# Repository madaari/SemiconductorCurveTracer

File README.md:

# SemiconductorCurveTracer
All the data related to Semiconductor Curve Tracer.

This Repo contains the design files, code files of every version of curve tracer
build at TI-CEPD.

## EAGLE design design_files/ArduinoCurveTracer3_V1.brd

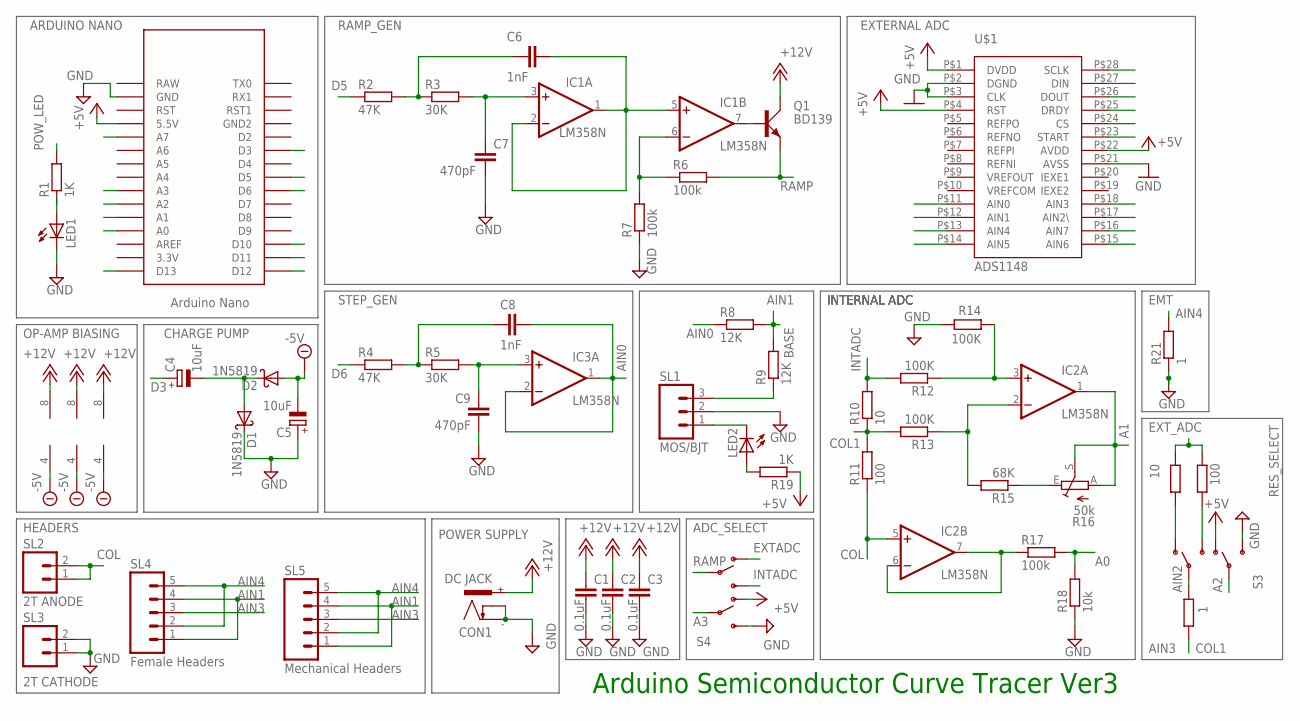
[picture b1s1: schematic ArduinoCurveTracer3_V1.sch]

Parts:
ARDUINONANO: NANO
C1, C2, C3: 0.1uF; C0805
C4, C5: 10uF; E2,5-5
C6: 1nF; C0603
C7: 470pF; C025-024X044
C8: 1nF; C025-024X044
C9: 470pF; C0805
CON1: DC JACK; NEB21R
D1, D2: 1N5819; DO41-10
IC1, IC2, IC3: LM358N; DIL08
LED1, LED2: LED3MM
Q1: BD139; TO126AV
R1, R19: 1K; 0207/10
R2: 47K; 0207/10
R3, R5: 30K; 0204/7
R4: 47K; 0204/7
R6: 100k; M0805
R7, R17: 100k; 0207/7
R8, R9: 12K; 0207/10
R10: 10; 0207/10
R11: 100; 0207/10
R12, R13: 100K; 0207/10
R14: 100K; 0204/7
R15: 68K; 0204/7
R16: 50k; S64W
R18: 10k; 0204/7
R21: 1; 0207/10
R22: 10; 0204/7
R23: 100; 0204/7
R24: 1; 0204/7
S3, S4: SWITCH-SPDTPTH2; SWITCHE-DPDT
SL1: MOS/BJT; 03P
SL2: 2T ANODE; 02P
SL3: 2T CATHODE; 02P
SL4: Female Headers; 05P
SL5: Mechanical Headers; 05P
U$1: ADS1148; TSSOP-28

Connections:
+5V: ARDUINONANO.5V (5.5V), R19.1, S3.4, S4.4, U$1.P$1 (DVDD), U$1.P$4 (RST), U$1.P$22 (AVDD)
+12V: C1.1, C2.1, C3.1, CON1.+, IC1.8 (V+), IC2.8 (V+), IC3.8 (V+), Q1.C
-5V: C5.-, D2.A, IC1.4 (V-), IC2.4 (V-), IC3.4 (V-)
A0: ARDUINONANO.A0, R17.2, R18.2
A1: ARDUINONANO.A1, IC2.1 (OUT), R16.A, R16.S
A2: ARDUINONANO.A2, S3.5
A3: ARDUINONANO.A3, S4.5
AIN0: C8.2, IC3.1 (OUT), IC3.2 (-IN), R8.1, U$1.P$11 (AIN0)
AIN1: R8.2, R9.2, SL4.1, SL4.4, SL5.1, SL5.4, U$1.P$12 (AIN1)
AIN2: R24.1, S3.2, U$1.P$17 (AIN2\)
AIN3: R10.1, R11.2, R13.2, R24.2, SL4.3, SL5.3, U$1.P$18 (AIN3)
AIN4: R21.2, SL4.2, SL4.5, SL5.2, SL5.5, U$1.P$13 (AIN4)
AIN5: U$1.P$14 (AIN5)
AIN6: U$1.P$15 (AIN6)
AIN7: U$1.P$16 (AIN7)
COL: IC2.5 (+IN), R11.1, SL2.1, SL2.2
CS: ARDUINONANO.D10, U$1.P$24 (CS)
D3: ARDUINONANO.D3, C4.+
D5: ARDUINONANO.D5, R2.1
D6: ARDUINONANO.D6, R4.1
DIN: ARDUINONANO.D11, U$1.P$27 (DIN)
DOUT: ARDUINONANO.D12, U$1.P$26 (DOUT)
DRDY: U$1.P$25 (DRDY)
EXTADC: R22.2, R23.2, S4.1
GND: ARDUINONANO.GND, C1.2, C2.2, C3.2, C5.+, C7.2, C9.1, CON1.-, CON1.C, D1.C, LED1.K (C), R7.1, R14.1, R18.1, R21.1, S3.6, S4.6, SL1.2, SL3.1, SL3.2, U$1.P$2 (DGND), U$1.P$3 (CLK), U$1.P$21 (AVSS)
INTADC: R10.2, R12.2, S4.3
unnamed: C4.-, D1.A, D2.C
unnamed: R9.1, SL1.3
unnamed: C6.1, R2.2, R3.1
unnamed: C7.1, IC1.3 (+IN), R3.2
unnamed: IC1.7 (OUT), Q1.B
unnamed: LED2.K (C), SL1.1
unnamed: IC1.6 (-IN), R6.1, R7.2
unnamed: C8.1, R4.2, R5.1
unnamed: C9.2, IC3.3 (+IN), R5.2
unnamed: LED2.A, R19.2
unnamed: R22.1, S3.1
unnamed: IC2.3 (+IN), R12.1, R14.2
unnamed: IC2.2 (-IN), R13.1, R15.2
unnamed: IC2.6 (-IN), IC2.7 (OUT), R17.1
unnamed: R15.1, R16.E
unnamed: LED1.A, R1.1
unnamed: R23.1, S3.3
POW_LED: ARDUINONANO.A7, R1.2
RAMP: C6.2, IC1.1 (OUT), IC1.2 (-IN), IC1.5 (+IN), Q1.E, R6.2, S4.2
SCLK: ARDUINONANO.D13, U$1.P$28 (SCLK)
START: U$1.P$23 (START)

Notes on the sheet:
Arduino Semiconductor Curve Tracer Ver3
EMT
POWER SUPPLY
CHARGE PUMP
OP-AMP BIASING
COL1
BASE
RES_SELECT
INTADC
ADC_SELECT
HEADERS
AIN2
AIN3
AIN1
RAMP_GEN
STEP_GEN
EXT_ADC
AIN4
RAMP
EXTADC
EXTERNAL ADC
POW_LED
ARDUINO NANO
INTERNAL ADC

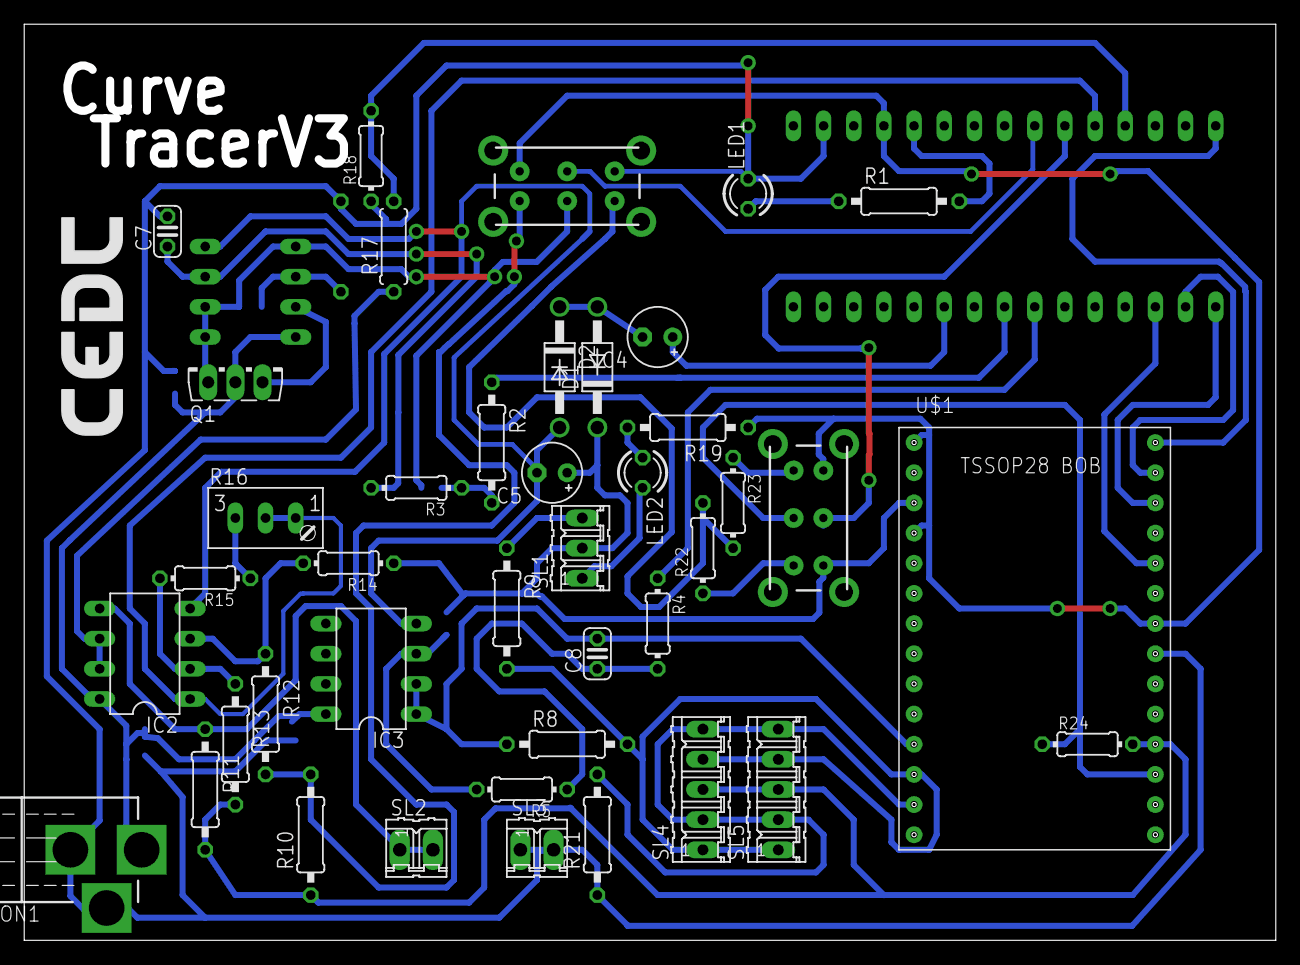
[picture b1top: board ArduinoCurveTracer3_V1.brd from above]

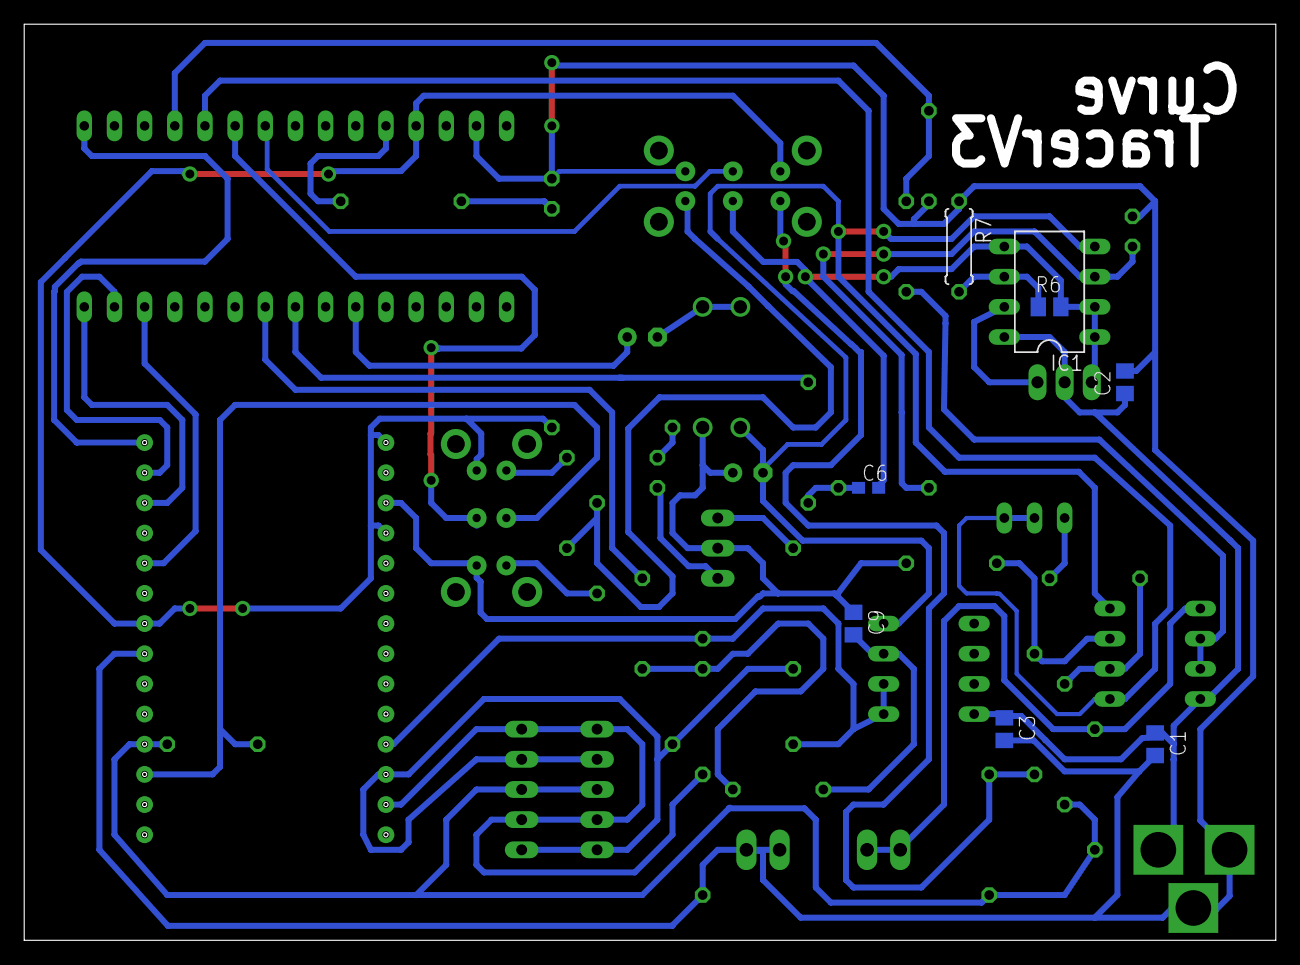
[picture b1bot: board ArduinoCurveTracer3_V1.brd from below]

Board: 2 copper layers, 105.4 x 77.1 mm, 51 parts (8 on the bottom side), 42 nets.

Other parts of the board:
U$2: LOGO-CEDT-SILK-18MM

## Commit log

2018-03-29 Added license
2018-03-29 Create LICENSE
2018-03-29 Added GUI files and images
2018-03-29 Updated GUI and generated python files
2018-03-30 Added event handler for window 1
2018-03-30 Added event handlers for window 2
2018-03-31 Added event handlers for window 3
2018-03-31 Resolved OS specific dependencies
2018-03-31 Added Linux standalone files
2019-12-09 Update LICENSE; Add code files; Add documentation; Add design files
